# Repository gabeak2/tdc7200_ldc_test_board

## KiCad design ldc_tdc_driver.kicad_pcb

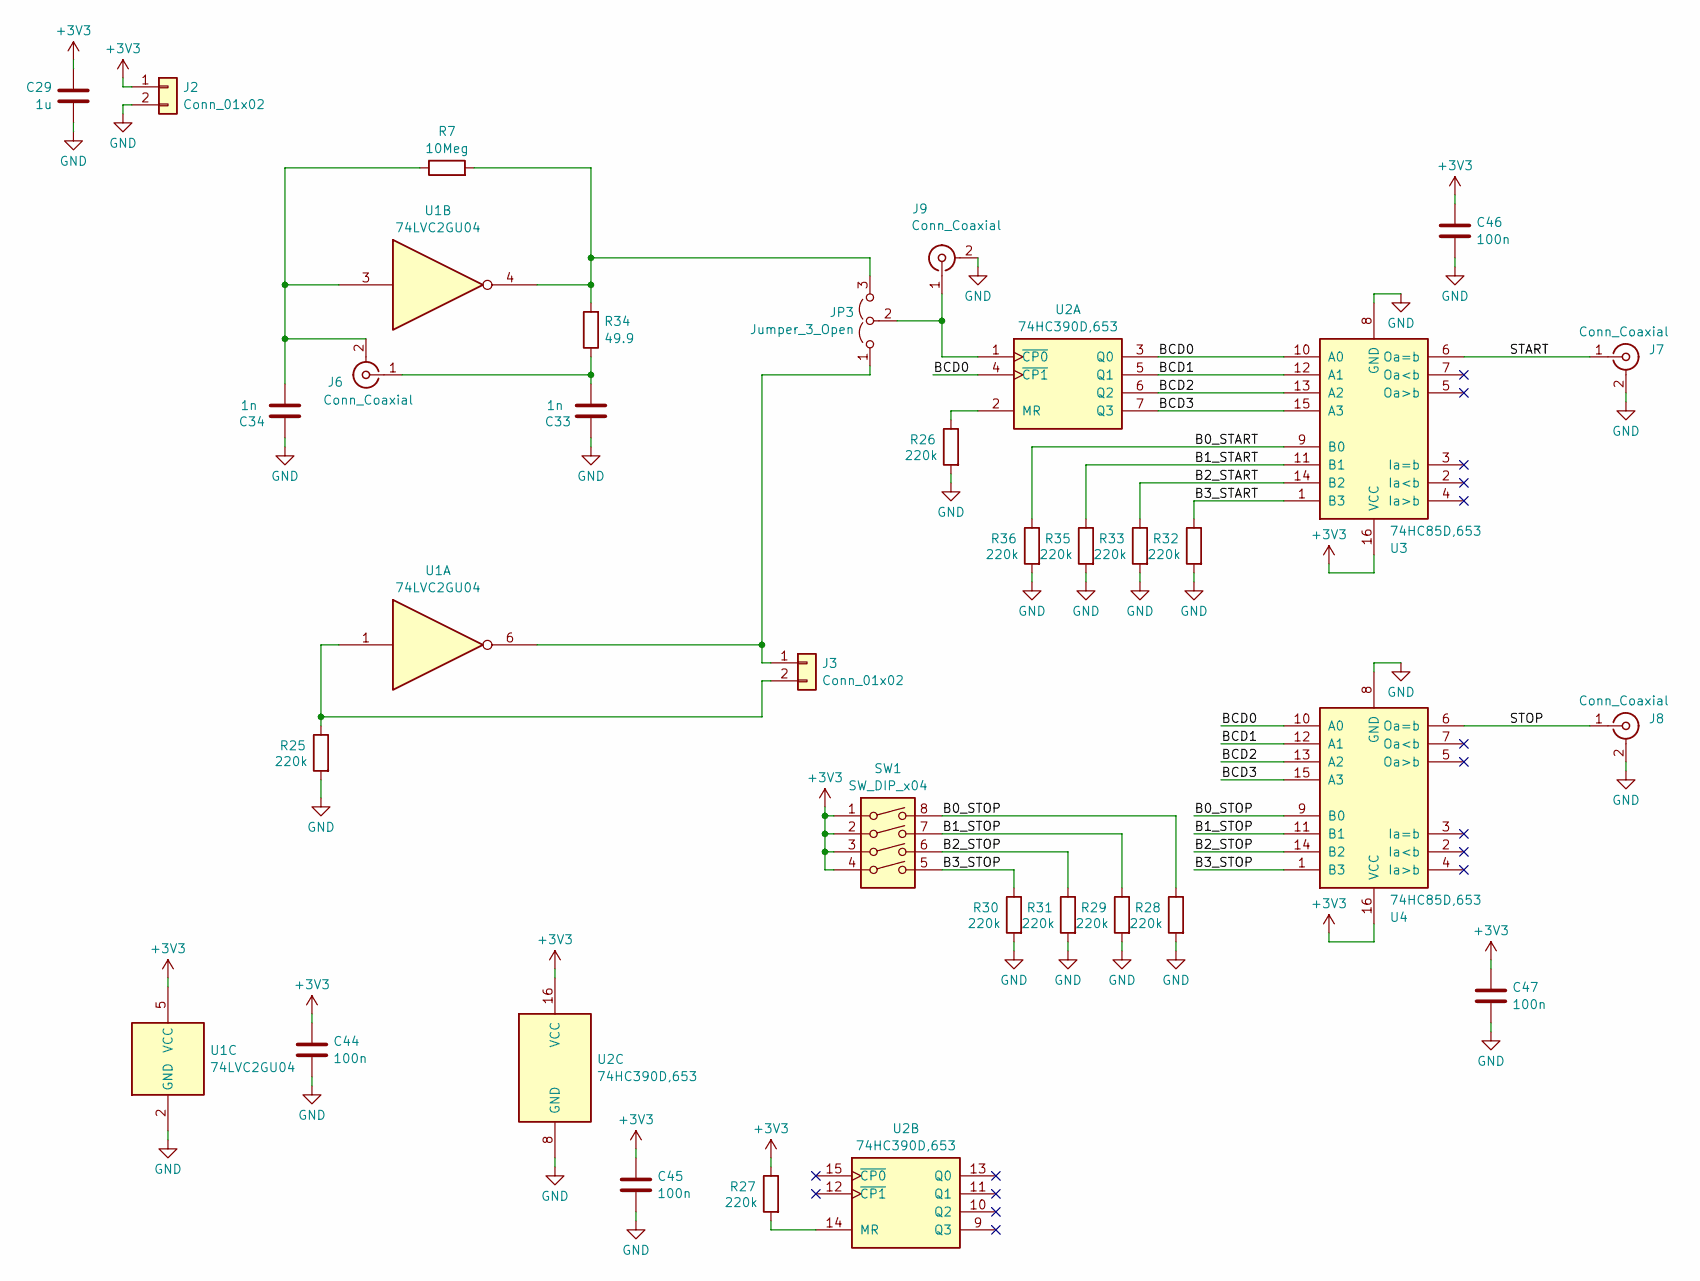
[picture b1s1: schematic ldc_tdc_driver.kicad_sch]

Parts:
C29: 1u; C_0603_1608Metric; LCSC C15849
C33, C34: 1n; C_0603_1608Metric; LCSC C1588
C44, C45, C46, C47: 100n; C_0603_1608Metric; LCSC C14663
J2, J3: Conn_01x02; PinSocket_1x02_P2.54mm_Vertical
J6, J7, J8, J9: Conn_Coaxial; SMA_BAT_Wireless_BWSMA-KWE-Z001; LCSC C496551
JP3: Jumper_3_Open; SolderJumper-3_P1.3mm_Open_Pad1.0x1.5mm
R7: 10Meg; R_0603_1608Metric; LCSC C7250
R25, R26, R27, R28, R29, R30, R31, R32, R33, R35, R36: 220k; R_0603_1608Metric; LCSC C22961
R34: 49.9; R_0603_1608Metric; LCSC C23185
SW1: SW_DIP_x04; SW_DIP_SPSTx04_Slide_Copal_CHS-04B_W7.62mm_P1.27mm; LCSC C3293144
U1: 74LVC2GU04; SOT-23-6; LCSC C139427
U2: 74HC390D,653; SOIC-16_3.9x9.9mm_P1.27mm; LCSC C5440882
U3, U4: 74HC85D,653; SOIC-16_3.9x9.9mm_P1.27mm; LCSC C5953

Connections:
+3V3: C29.1, C44.1, C45.1, C46.1, C47.1, J2.1, R27.1, SW1.1, SW1.2, SW1.3, SW1.4, U1.5 (VCC), U2.16 (VCC), U3.16 (VCC), U4.16 (VCC)
/B0_START: R36.1, U3.9 (B0)
/B0_STOP: R28.1, SW1.8, U4.9 (B0)
/B1_START: R35.1, U3.11 (B1)
/B1_STOP: R29.1, SW1.7, U4.11 (B1)
/B2_START: R33.1, U3.14 (B2)
/B2_STOP: R31.1, SW1.6, U4.14 (B2)
/B3_START: R32.1, U3.1 (B3)
/B3_STOP: R30.1, SW1.5, U4.1 (B3)
/BCD0: U2.3 (Q0), U2.4 (~CP1), U3.10 (A0), U4.10 (A0)
/BCD1: U2.5 (Q1), U3.12 (A1), U4.12 (A1)
/BCD2: U2.6 (Q2), U3.13 (A2), U4.13 (A2)
/BCD3: U2.7 (Q3), U3.15 (A3), U4.15 (A3)
/START: J7.1 (In), U3.6 (Oa=b)
/STOP: J8.1 (In), U4.6 (Oa=b)
GND: C29.2, C33.1, C34.1, C44.2, C45.2, C46.2, C47.2, J2.2, J7.2 (Ext), J8.2 (Ext), J9.2 (Ext), R25.2, R26.2, R28.2, R29.2, R30.2, R31.2, R32.2, R33.2, R35.2, R36.2, U1.2 (GND), U2.8 (GND), U3.8 (GND), U4.8 (GND)
unnamed: J3.1, JP3.1 (A), U1.6
unnamed: J3.2, R25.1, U1.1
unnamed: C34.2, J6.2 (Ext), R7.1, U1.3
unnamed: C33.2, J6.1 (In), R34.1
unnamed: J9.1 (In), JP3.2 (C), U2.1 (~CP0)
unnamed: JP3.3 (B), R7.2, R34.2, U1.4
unnamed: R26.1, U2.2 (MR)
unnamed: R27.2, U2.14 (MR)

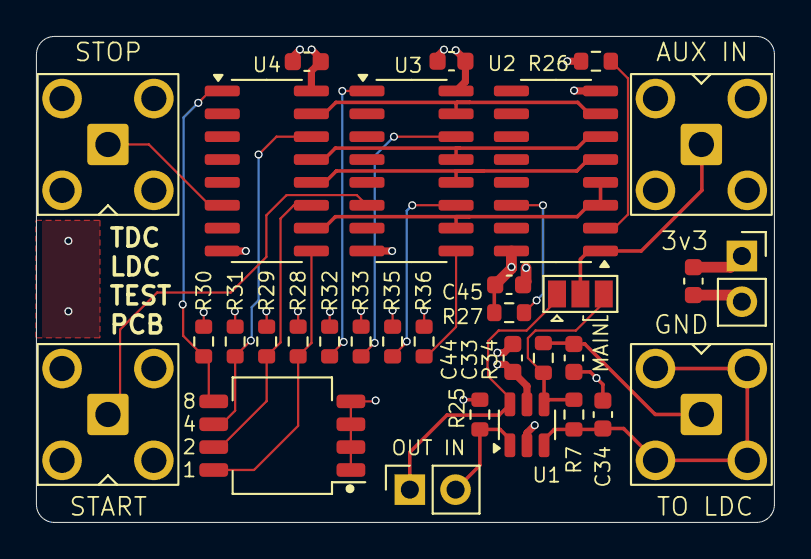
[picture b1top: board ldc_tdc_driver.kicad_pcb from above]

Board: 4 copper layers, 41.0 x 27.0 mm, 32 parts (0 on the bottom side), 24 nets.

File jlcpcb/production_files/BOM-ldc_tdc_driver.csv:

Comment,Designator,Footprint,LCSC,Quantity
74LVC2GU04,U1,SOT-23-6,C139427,1
100n,"C44,C45,C46,C47",C_0603_1608Metric,C14663,4
1u,C29,C_0603_1608Metric,C15849,1
1n,"C33,C34",C_0603_1608Metric,C1588,2
220k,"R25,R26,R27,R28,R29,R30,R31,R32,R33,R35,R36",R_0603_1608Metric,C22961,11
49.9,R34,R_0603_1608Metric,C23185,1
SW_DIP_x04,SW1,SW_DIP_SPSTx04_Slide_Copal_CHS-04B_W7.62mm_P1.27mm,C3293144,1
Conn_Coaxial,"J6,J7,J8,J9",SMA_BAT_Wireless_BWSMA-KWE-Z001,C496551,4
"74HC390D,653",U2,SOIC-16_3.9x9.9mm_P1.27mm,C5440882,1
"74HC85D,653","U3,U4",SOIC-16_3.9x9.9mm_P1.27mm,C5953,2
10Meg,R7,R_0603_1608Metric,C7250,1
Conn_01x02,J2,PinSocket_1x02_P2.54mm_Vertical,,1
Conn_01x02,J3,PinSocket_1x02_P2.54mm_Vertical,,1

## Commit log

2026-01-10 Initial commit, layout not done
2026-01-11 Finished layout
